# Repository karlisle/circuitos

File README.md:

# circuitos
Cosos de electronica

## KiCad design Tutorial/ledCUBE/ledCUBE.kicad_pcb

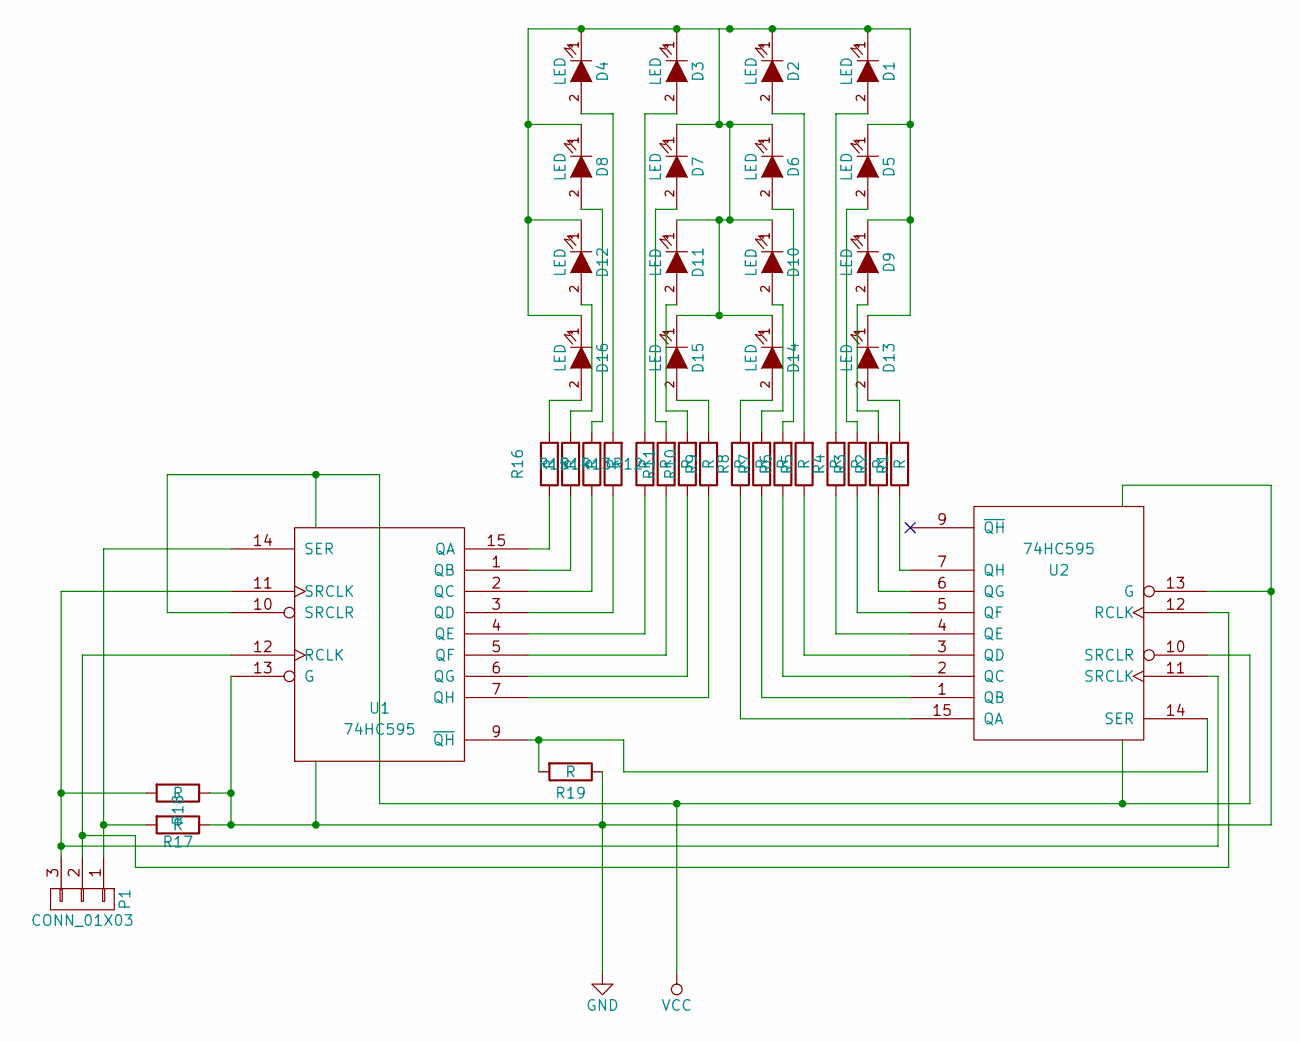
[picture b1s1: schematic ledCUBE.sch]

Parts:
D1, D2, D3, D4, D5, D6, D7, D8, D9, D10, D11, D12, D13, D14, D15, D16: LED; LED-3MM
P1: CONN_01X03; Socket_Strip_Straight_1x03
R1, R2, R3, R4, R5, R6, R7, R8, R9, R10, R11, R12, R13, R14, R15, R16, R17, R18, R19: R; Resistor_Horizontal_RM10mm
U1, U2: 74HC595; DIP-16_W7.62mm

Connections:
GND: R17.1, R18.1, R19.1, U1.8 (GND), U1.13 (G), U2.8 (GND), U2.13 (G)
unnamed: D1.2 (A), R4.2
unnamed: D2.2 (A), R5.2
unnamed: D3.2 (A), R12.2
unnamed: D4.2 (A), R13.2
unnamed: D5.2 (A), R3.2
unnamed: D6.2 (A), R6.2
unnamed: D7.2 (A), R11.2
unnamed: D9.2 (A), R2.2
unnamed: D6.1 (K), D7.1 (K), D10.1 (K), D11.1 (K), D14.1 (K), D15.1 (K)
unnamed: D10.2 (A), R7.2
unnamed: D11.2 (A), R10.2
unnamed: D12.2 (A), R15.2
unnamed: D13.2 (A), R1.2
unnamed: D14.2 (A), R8.2
unnamed: D15.2 (A), R9.2
unnamed: D16.2 (A), R16.2
unnamed: P1.1, R17.2, U1.14 (SER)
unnamed: P1.2, U1.12 (RCLK), U2.12 (RCLK)
unnamed: P1.3, R18.2, U1.11 (SRCLK), U2.11 (SRCLK)
unnamed: R1.1, U2.7 (QH)
unnamed: R2.1, U2.6 (QG)
unnamed: R3.1, U2.5 (QF)
unnamed: R4.1, U2.4 (QE)
unnamed: R5.1, U2.3 (QD)
unnamed: R6.1, U2.2 (QC)
unnamed: R7.1, U2.1 (QB)
unnamed: R8.1, U2.15 (QA)
unnamed: R9.1, U1.7 (QH)
unnamed: R10.1, U1.6 (QG)
unnamed: R11.1, U1.5 (QF)
unnamed: R12.1, U1.4 (QE)
unnamed: R13.1, U1.3 (QD)
unnamed: R14.1, U1.2 (QC)
unnamed: R15.1, U1.1 (QB)
unnamed: R16.1, U1.15 (QA)
unnamed: R19.2, U1.9 (~QH), U2.14 (SER)
VCC: U1.10 (SRCLR), U1.16 (VCC), U2.10 (SRCLR), U2.16 (VCC)

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
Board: 2 copper layers, 38 parts (0 on the bottom side), 40 nets, no tracks yet.

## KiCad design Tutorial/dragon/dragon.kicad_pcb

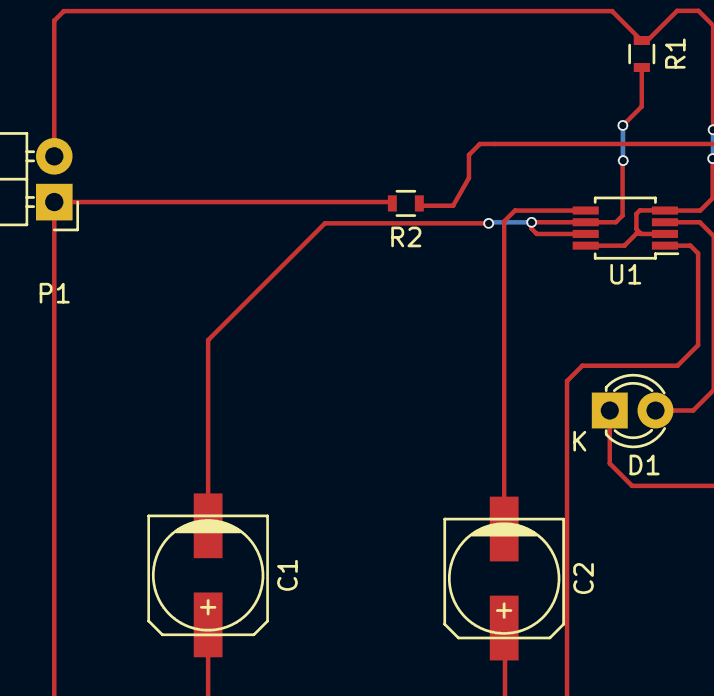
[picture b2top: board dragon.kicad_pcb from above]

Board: 2 copper layers, 7 parts (0 on the bottom side), 6 nets.

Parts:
C1, C2: CP; c_elec_6.3x4.5
D1: LED; LED-3MM
P1: CONN_01X02; Pin_Header_Angled_1x02
R1, R2: R; R_0603
U1: LM555N; MSOP-8_3x3mm_Pitch0.65mm

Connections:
GND: C1.1, C2.1, P1.1, R2.2, U1.1
unnamed: C1.2, R1.2, U1.6, U1.7
unnamed: C2.2, U1.5
unnamed: D1.1, R2.1
unnamed: D1.2, U1.3
VCC: P1.2, R1.1, U1.2, U1.4, U1.8

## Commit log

2016-03-12 cubo de leds
